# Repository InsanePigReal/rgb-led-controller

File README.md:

# rgb-led-controller

# High-Current RGB LED Controller (24V)

A compact (30.99 mm* 32.07 mm = <1000mm^2), high efficiency PWM controller designed to drive 24V RGB LED strips using logic-level mosfets.

## Aims

- Design a small controller for an LED strip so that I can control LEDs in my house without a large, bulky controller -> the PCB must also be able to be easily mounted.
    - Previously, I controlled LEDs using components on a perfboard, however that was difficult to mount and organise with the amount of cables.
- The components must be cheap, as controllers can be purchased online for £10.
- Must functon at 24v, as the LEDs I have work at 24v.

## Specifications
- Input -> 24V - (IRLML6344 functions up to 30v)
- Control Logic -> 3.3v or 5v (micocontroller compatible) - (IRLML6344 functions up to 12v)
- Max Current -> 4A (per channel) - (limited by IRLML6344 Ip)
- Switching Frequency -> Tested up to 20kHz PWM

## Design Justification
- Trace widths:
    - Main power rails utilize 2mm traces. Based on IPC-2221 standards, this means that the traces can handle the max current of 4A.
    - Signal traces utilised 0.3mm traces, as they will not be carrying significant current (only control mosfet gates)

- Component selection:
    - IRLML6344
        - low gate threshold voltage - Vgs(th) - (0.5-1.1v), allowing it be driven with a 3.3v micocontroller signal without needing a gate driver.
        - Rated for Vds = 30v, providing a safe margin for 24v LEDs
        - Low on-resitance - Rds(on) = 29-37mΩ - minimises power dissipation, keeping the SOT-23 package cool when driving several amps of current
    - A mosfet was chosen instead of a relay due to its faster switching potential
        - This is useful for turning RGB LED strips on/off quickly -> for example, for decoration, where a mosfet will appear more seamless
        - Mosfets additonally consume less power, which is useful as the LED strips will be turned on for a large portion of the time (such as when the user is at work)
        - Mosfets are additionally more compact, which fufills one of the aims of the project (a compact RGB LED Controller
    - 100R Gate Resistor
        - Protects MCU GPIO by limiting peak current to (3.3V/100Ω=33mA)
    - 100K Pull-Down Resistor
        - Prevent floating GPIOs from causing the LEDs to flicker
        - 100K was chosen as a "weak" pull-down -> strong enough to bleed off charge but high enough to not wase significant power during operation
    - 100uF bulk electrolytic capacitor
        - Rated for 25V to ensure it can handle 24V load
        - Prevent voltage dips when switching
    - 100nF decoupling ceramic capacitor
        - Filter out high frequency noise from PWM switching -> ensures LED doesn't flicker

- Thermal managment: Added a large ground pour on the bottom layer, which will act as a heatsink for the SOT-23 mosfets.
    - SOT-23 Package can dissipate ≈ 1.25W
        - At 2A load, P = 2^2 * 0.037 = 0.148W -> design operates at a 8x safety factor regarding thermals
        - At 4A load, P = 4^2 * 0.037 = 0.592W -> design operates at a 2x safety factor regarding thermals

## Iteration and Improvements

1st version was not compact, meaning that it would not fit in tight spaces like I desired, as well as it being difficult to mount. Additionally, the capacitors were too far from the power supply, which would have lead to less stability and performance. Additionally, the length of the traces meant higher resistance and less signal integrity. Also, this design has no power input and no vias, so it would not have been functional.

2nd version improved on capacitor placement, as well as trace length and overall size. Additionally, it now included power input. However, some of the traces (such as the signal traces) were 90 degrees, which would be bad for manufacturability and signal integrity. Additionally, though I included vias, they would not be able to manufactured due to improper sizing.
Issues include the lack of moutning holes, as well as not using a ground pour and using a lot of ground traces, which created a higher impedance path. Additionally, a solid fill was used on the 24v plane, which would have made the PCB more difficult to hand solder.

Final version added mounting holes for the PCB, making it a more user-friendly design. Additionally, a ground pour was used instead of a the 'spider' of ground traces, and a thermal relief fill was used to make hand-soldering easier. Fixed the traces that were 90 degrees - now all traces are 45 degrees max. Furthermore, I changed the via diameter and hole size so that it fits with the chosen manufactuer's specifications. More vias were used than previously to ensure minimal voltage loss based on current.

# License
This project is licensed under the MIT License - see the LICENSE file for details

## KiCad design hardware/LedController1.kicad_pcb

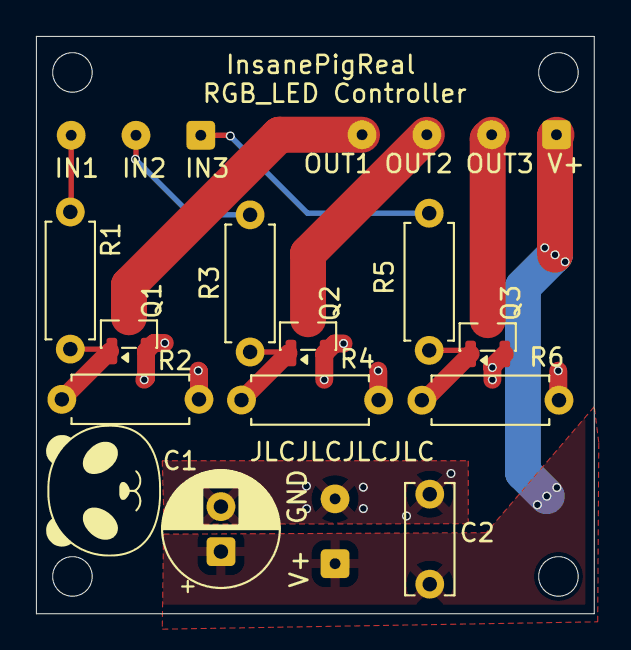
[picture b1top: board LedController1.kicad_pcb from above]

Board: 2 copper layers, 31.0 x 32.1 mm, 18 parts (0 on the bottom side), 11 nets.

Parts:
C1: 100uf; CP_Radial_D6.3mm_P2.50mm
C2: 100nf; C_Disc_D6.0mm_W2.5mm_P5.00mm
H1, H1#2, H1#3, H1#4: MountingHole; MountingHole_2.2mm_M2
J2: Conn_01x03_Pin; SolderWire-0.1sqmm_1x03_P3.6mm_D0.4mm_OD1mm
Q1, Q2, Q3: IRLML6344; SOT-23
R1, R3, R5: 100R; R_Axial_DIN0207_L6.3mm_D2.5mm_P7.62mm_Horizontal
R2, R4, R6: 100K; R_Axial_DIN0207_L6.3mm_D2.5mm_P7.62mm_Horizontal
V+: Conn_01x02_Pin; SolderWire-0.1sqmm_1x02_P3.6mm_D0.4mm_OD1mm
V+#2: Conn_01x04_Pin; SolderWire-0.1sqmm_1x04_P3.6mm_D0.4mm_OD1mm

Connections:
+24V: C1.1, C2.1, V+.1, V+#2.1
GND: C1.2, C2.2, Q1.2 (S), Q2.2 (S), Q3.2 (S), R2.2, R4.2, R6.2, V+.2
unnamed: Q3.3 (D), V+#2.2
unnamed: Q2.3 (D), V+#2.3
unnamed: Q1.3 (D), V+#2.4
unnamed: J2.1, R5.1
unnamed: J2.2, R3.1
unnamed: J2.3, R1.1
unnamed: Q1.1 (G), R1.2, R2.1
unnamed: Q2.1 (G), R3.2, R4.1
unnamed: Q3.1 (G), R5.2, R6.1

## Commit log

2026-02-19 Added Kicad project files
2026-02-19 Added asset files for images of PCB and Schematic
2026-02-20 Added Kicad files
2026-02-20 Added Gerber files for manufacturing
2026-02-20 Uploaded render of the PCB
2026-02-20 Create LICENSE
